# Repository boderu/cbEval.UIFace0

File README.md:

# cbEval.ATtiny412_1614

Evaluation-Board - User-Interface mit Display, Tastern, Drehimpolsgebern und Soundausgabe

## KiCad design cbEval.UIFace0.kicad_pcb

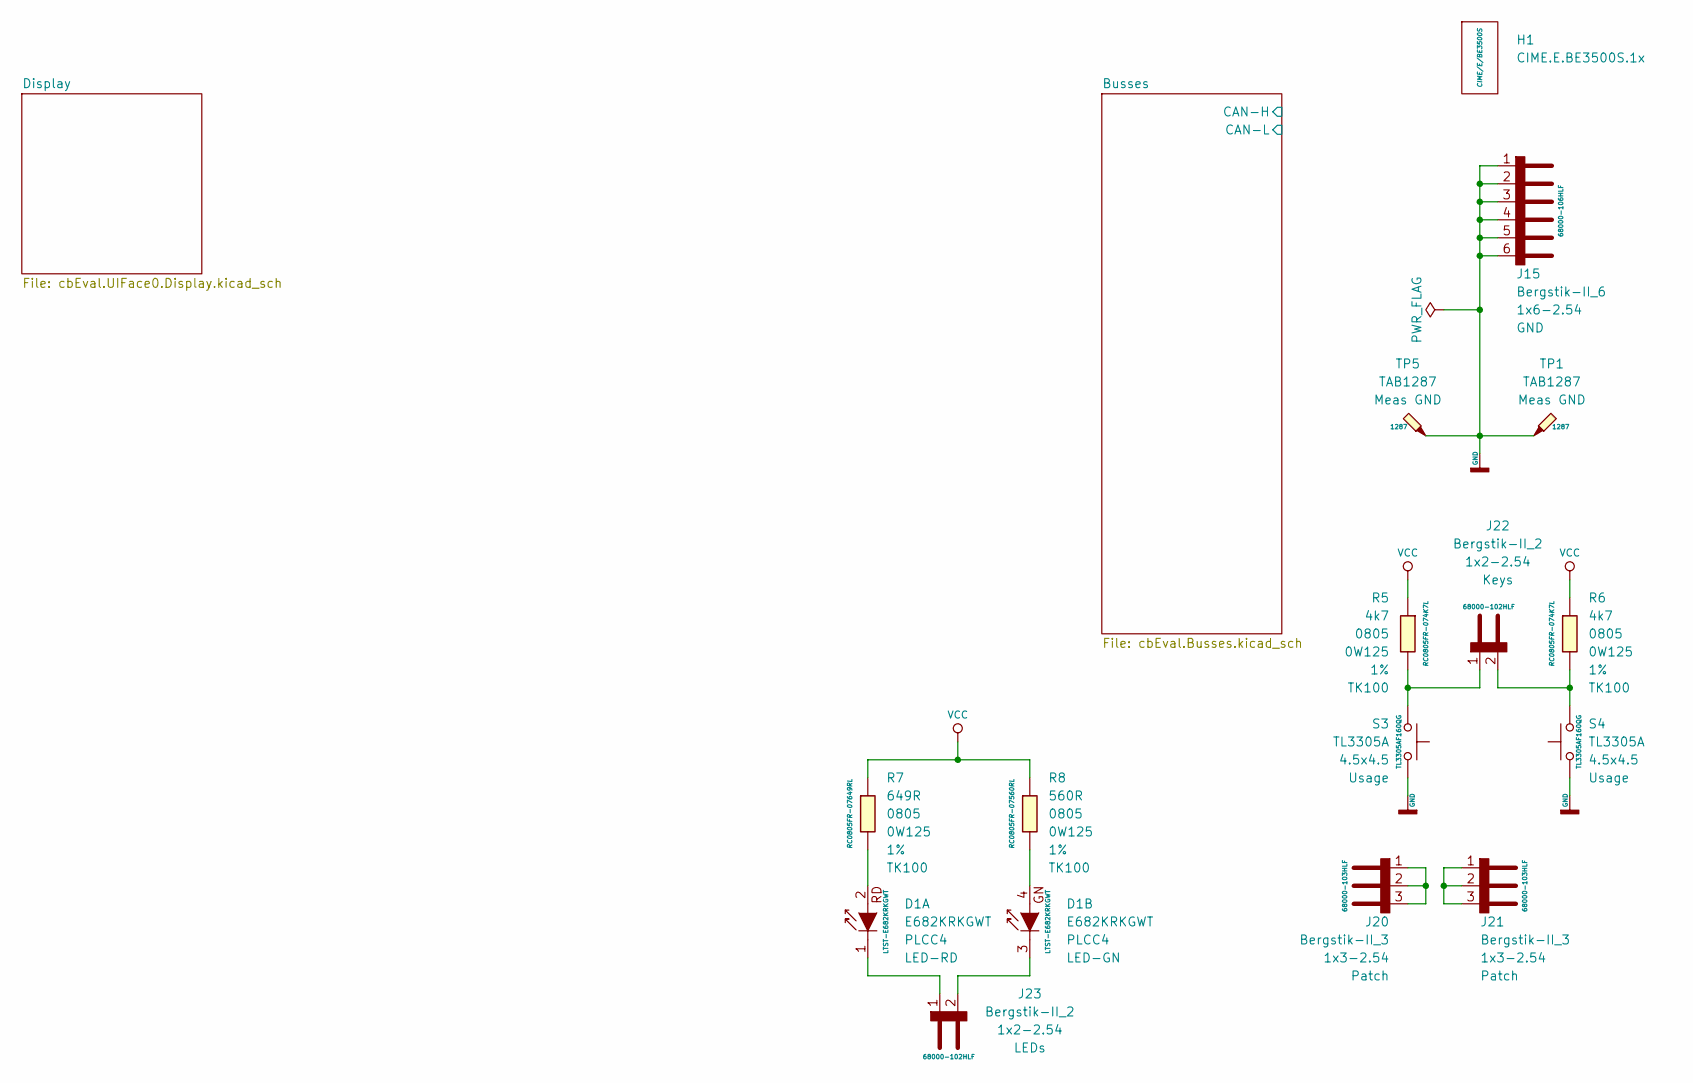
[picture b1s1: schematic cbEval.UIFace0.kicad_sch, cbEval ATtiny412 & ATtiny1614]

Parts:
D1: E682KRKGWT; LED_Avago_PLCC4_3.2x2.8mm_CW
H1: CIME.E.BE3500S.1x; Camdenboss.CIME.E.BE3500S.1x
J15: Bergstik-II_6; PinHeader_1x06_P2.54mm_Vertical
J20, J21: Bergstik-II_3; PinHeader_1x03_P2.54mm_Vertical
J22, J23: Bergstik-II_2; PinHeader_1x02_P2.54mm_Vertical
R5, R6: 4k7; R_0805_2012Metric; Tolerance 1%
R7: 649R; R_0805_2012Metric; Tolerance 1%
R8: 560R; R_0805_2012Metric; Tolerance 1%
S3, S4: TL3305A; SW_SPST_TL3305A
TP1, TP5: TAB1287; TestPoint_Bridge_Pitch5.08mm_Drill1.3mm

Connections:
GND: J15.1 (A1), J15.2 (A2), J15.3 (A3), J15.4 (A4), J15.5 (A5), J15.6 (A6), S3.2, S4.2, TP1.1, TP5.1; also elsewhere on the board
unnamed: D1.1 (Rd-C), J23.1 (A1)
unnamed: D1.2 (Rd-A), R7.2
unnamed: D1.3 (Gn-C), J23.2 (A2)
unnamed: D1.4 (Gn-A), R8.2
unnamed: J20.1 (A1), J20.2 (A2), J20.3 (A3)
unnamed: J21.1 (A1), J21.2 (A2), J21.3 (A3)
unnamed: J22.1 (A1), R5.2, S3.1
unnamed: J22.2 (A2), R6.2, S4.1
VCC: R5.1, R6.1, R7.1, R8.1; also elsewhere on the board

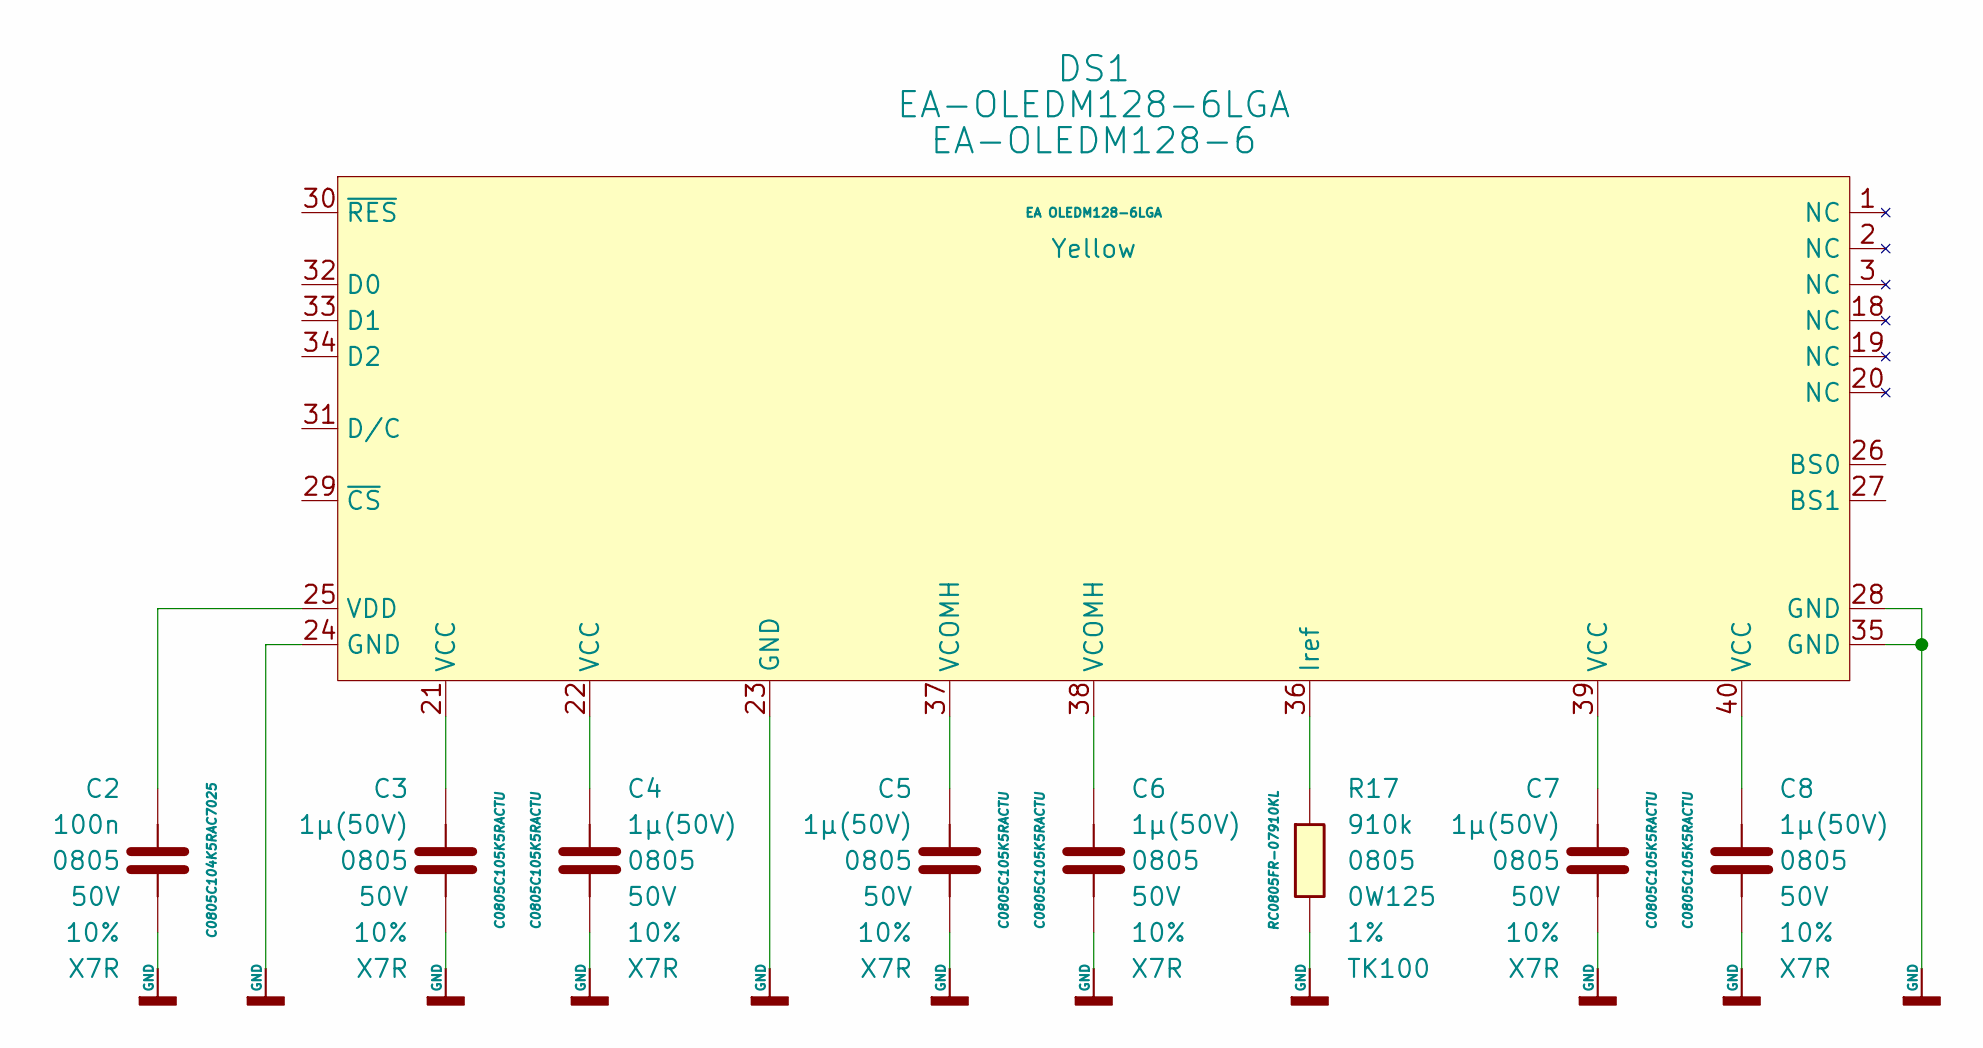
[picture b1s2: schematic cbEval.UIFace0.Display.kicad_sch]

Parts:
C2: 100n; C_0805_2012Metric; Voltage 50V; Tolerance 10%
C3, C4, C5, C6, C7, C8: 1µ(50V); C_0805_2012Metric; Voltage 50V; Tolerance 10%
DS1: EA-OLEDM128-6LGA; EA-OLEDM128-6
R17: 910k; R_0805_2012Metric; Tolerance 1%

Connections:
GND: C2.2, C3.2, C4.2, C5.2, C6.2, C7.2, C8.2, DS1.23 (GND), DS1.24 (GND), DS1.28 (GND), DS1.35 (GND), R17.2; also elsewhere on the board
unnamed: C2.1, DS1.25 (VDD)
unnamed: C3.1, DS1.21 (VCC)
unnamed: C4.1, DS1.22 (VCC)
unnamed: C5.1, DS1.37 (VCOMH)
unnamed: C6.1, DS1.38 (VCOMH)
unnamed: C7.1, DS1.39 (VCC)
unnamed: C8.1, DS1.40 (VCC)
unnamed: DS1.36 (Iref), R17.1

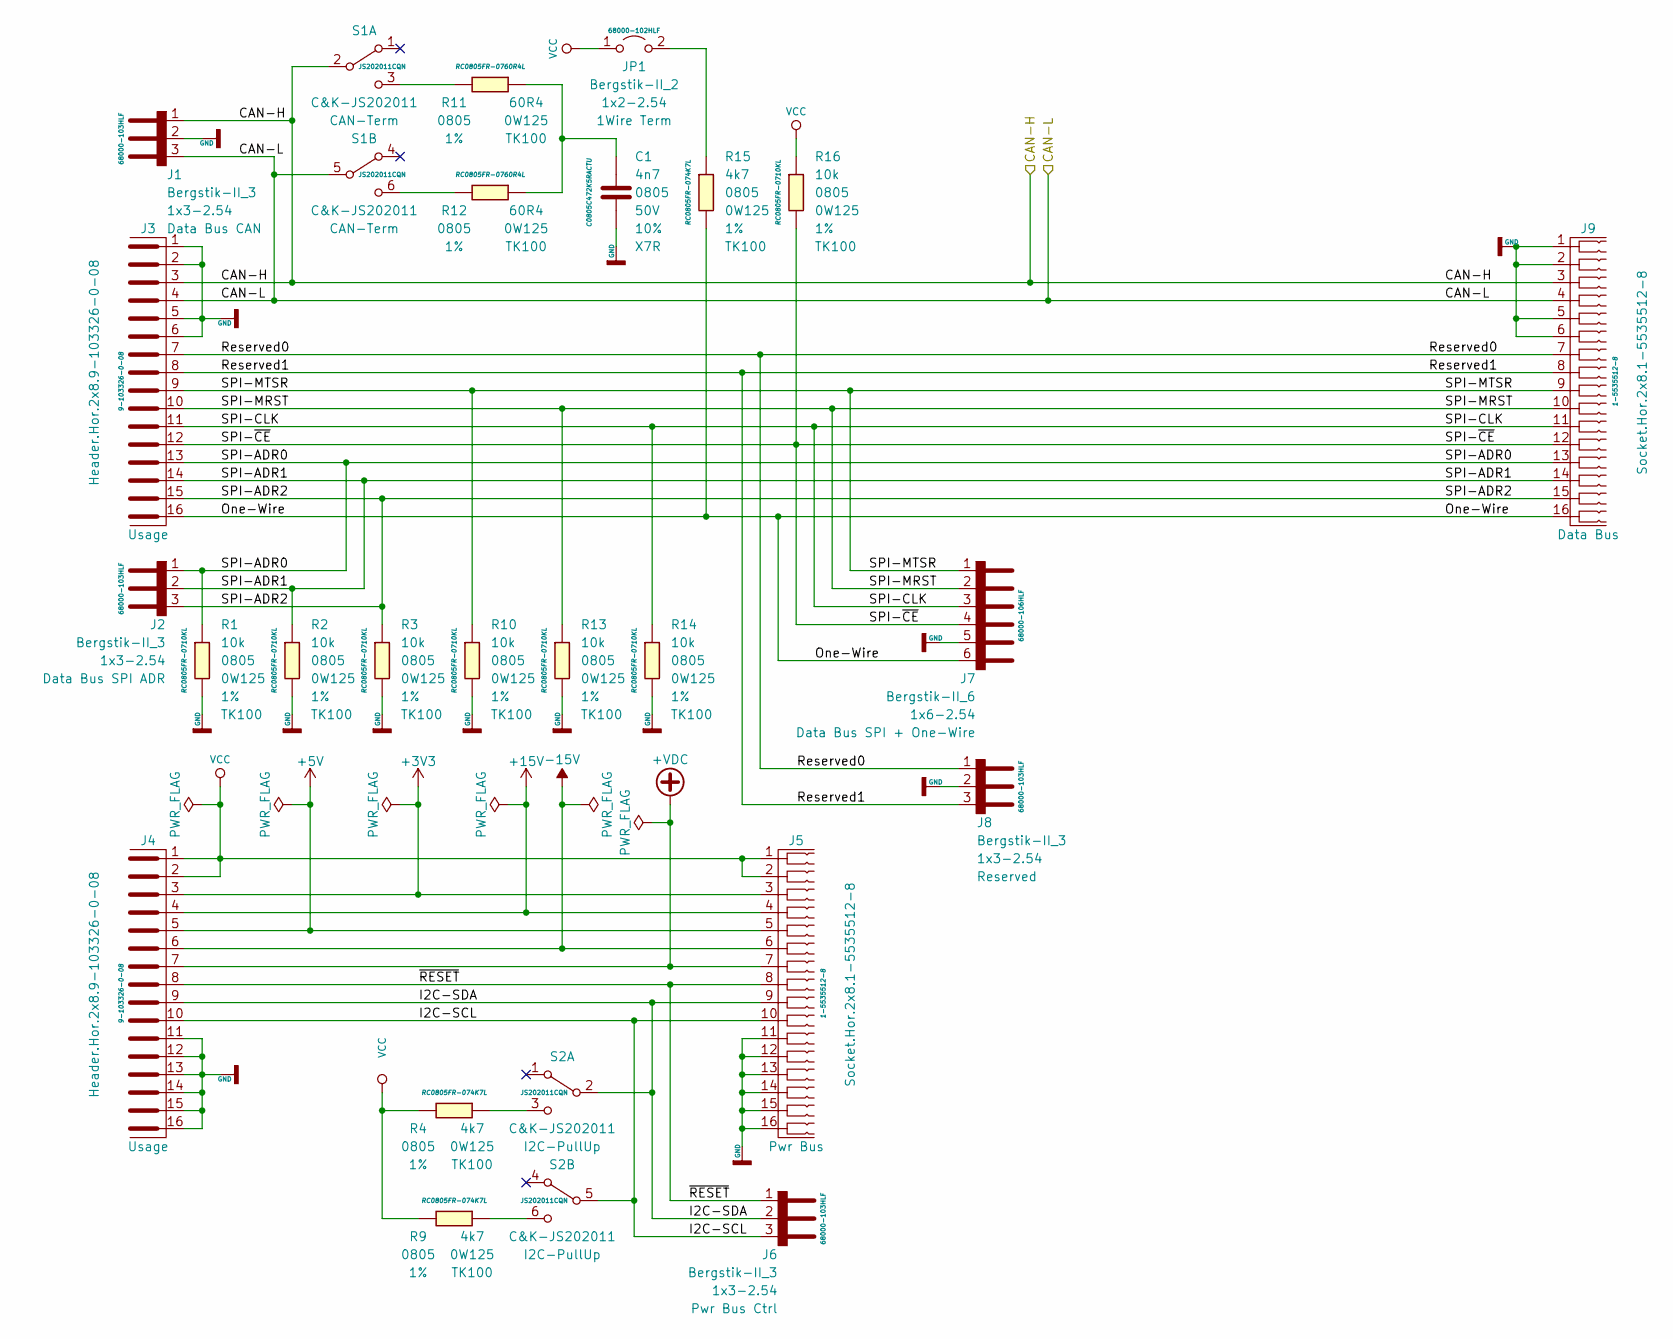
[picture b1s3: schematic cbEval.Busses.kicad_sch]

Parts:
C1: 4n7; C_0805_2012Metric; Voltage 50V; Tolerance 10%
J1, J2, J6, J8: Bergstik-II_3; PinHeader_1x03_P2.54mm_Vertical
J3, J4: Header.Hor.2x8.9-103326-0-08; PinHeader_2x08_P2.54mm_Horizontal
J5, J9: Socket.Hor.2x8.1-5535512-8; Socket.Hor.2x5.6-5535512-4
J7: Bergstik-II_6; PinHeader_1x06_P2.54mm_Vertical
JP1: Bergstik-II_2; PinHeader_1x02_P2.54mm_Vertical
R1, R2, R3, R10, R13, R14, R16: 10k; R_0805_2012Metric; Tolerance 1%
R4, R9, R15: 4k7; R_0805_2012Metric; Tolerance 1%
R11, R12: 60R4; R_0805_2012Metric; Tolerance 1%
S1, S2: C&K-JS202011; SW_CuK_JS202011CQN_DPDT_Straight

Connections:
+3V3: J4.3, J5.3
+5V: J4.5, J5.5
+15V: J4.4, J5.4
+VDC: J4.7, J5.7
-15V: J4.6, J5.6
/Busses/CAN-H: J1.1 (A1), J3.3, J9.3, S1.2 (B)
/Busses/CAN-L: J1.3 (A3), J3.4, J9.4, S1.5 (B)
/Busses/I2C-SCL: J4.10, J5.10, J6.3 (A3), S2.5 (B)
/Busses/I2C-SDA: J4.9, J5.9, J6.2 (A2), S2.2 (B)
/Busses/One-Wire: J3.16, J7.6 (A6), J9.16, R15.2
/Busses/Reserved0: J3.7, J8.1 (A1), J9.7
/Busses/Reserved1: J3.8, J8.3 (A3), J9.8
/Busses/SPI-ADR0: J2.1 (A1), J3.13, J9.13, R1.1
/Busses/SPI-ADR1: J2.2 (A2), J3.14, J9.14, R2.1
/Busses/SPI-ADR2: J2.3 (A3), J3.15, J9.15, R3.1
/Busses/SPI-CLK: J3.11, J7.3 (A3), J9.11, R14.1
/Busses/SPI-MRST: J3.10, J7.2 (A2), J9.10, R13.1
/Busses/SPI-MTSR: J3.9, J7.1 (A1), J9.9, R10.1
/Busses/SPI-~CE: J3.12, J7.4 (A4), J9.12, R16.2
/Busses/~RESET: J4.8, J5.8, J6.1 (A1)
GND: C1.2, J1.2 (A2), J3.1, J3.2, J3.5, J3.6, J4.11, J4.12, J4.13, J4.14, J4.15, J4.16, J5.11, J5.12, J5.13, J5.14, J5.15, J5.16, J7.5 (A5), J8.2 (A2), J9.1, J9.2, J9.5, J9.6, R1.2, R2.2, R3.2, R10.2, R13.2, R14.2; also elsewhere on the board
unnamed: C1.1, R11.1, R12.1
unnamed: JP1.2 (B), R15.1
unnamed: R4.1, S2.3 (C)
unnamed: R9.1, S2.6 (C)
unnamed: R11.2, S1.3 (C)
unnamed: R12.2, S1.6 (C)
VCC: J4.1, J4.2, J5.1, J5.2, JP1.1 (A), R4.2, R9.2, R16.1; also elsewhere on the board

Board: 2 copper layers, 49 parts (0 on the bottom side), 44 nets, no tracks yet.

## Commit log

2022-02-13 Readme hinzugefügt
2022-02-13 Arbeiten am Projekt (Sicherung)
